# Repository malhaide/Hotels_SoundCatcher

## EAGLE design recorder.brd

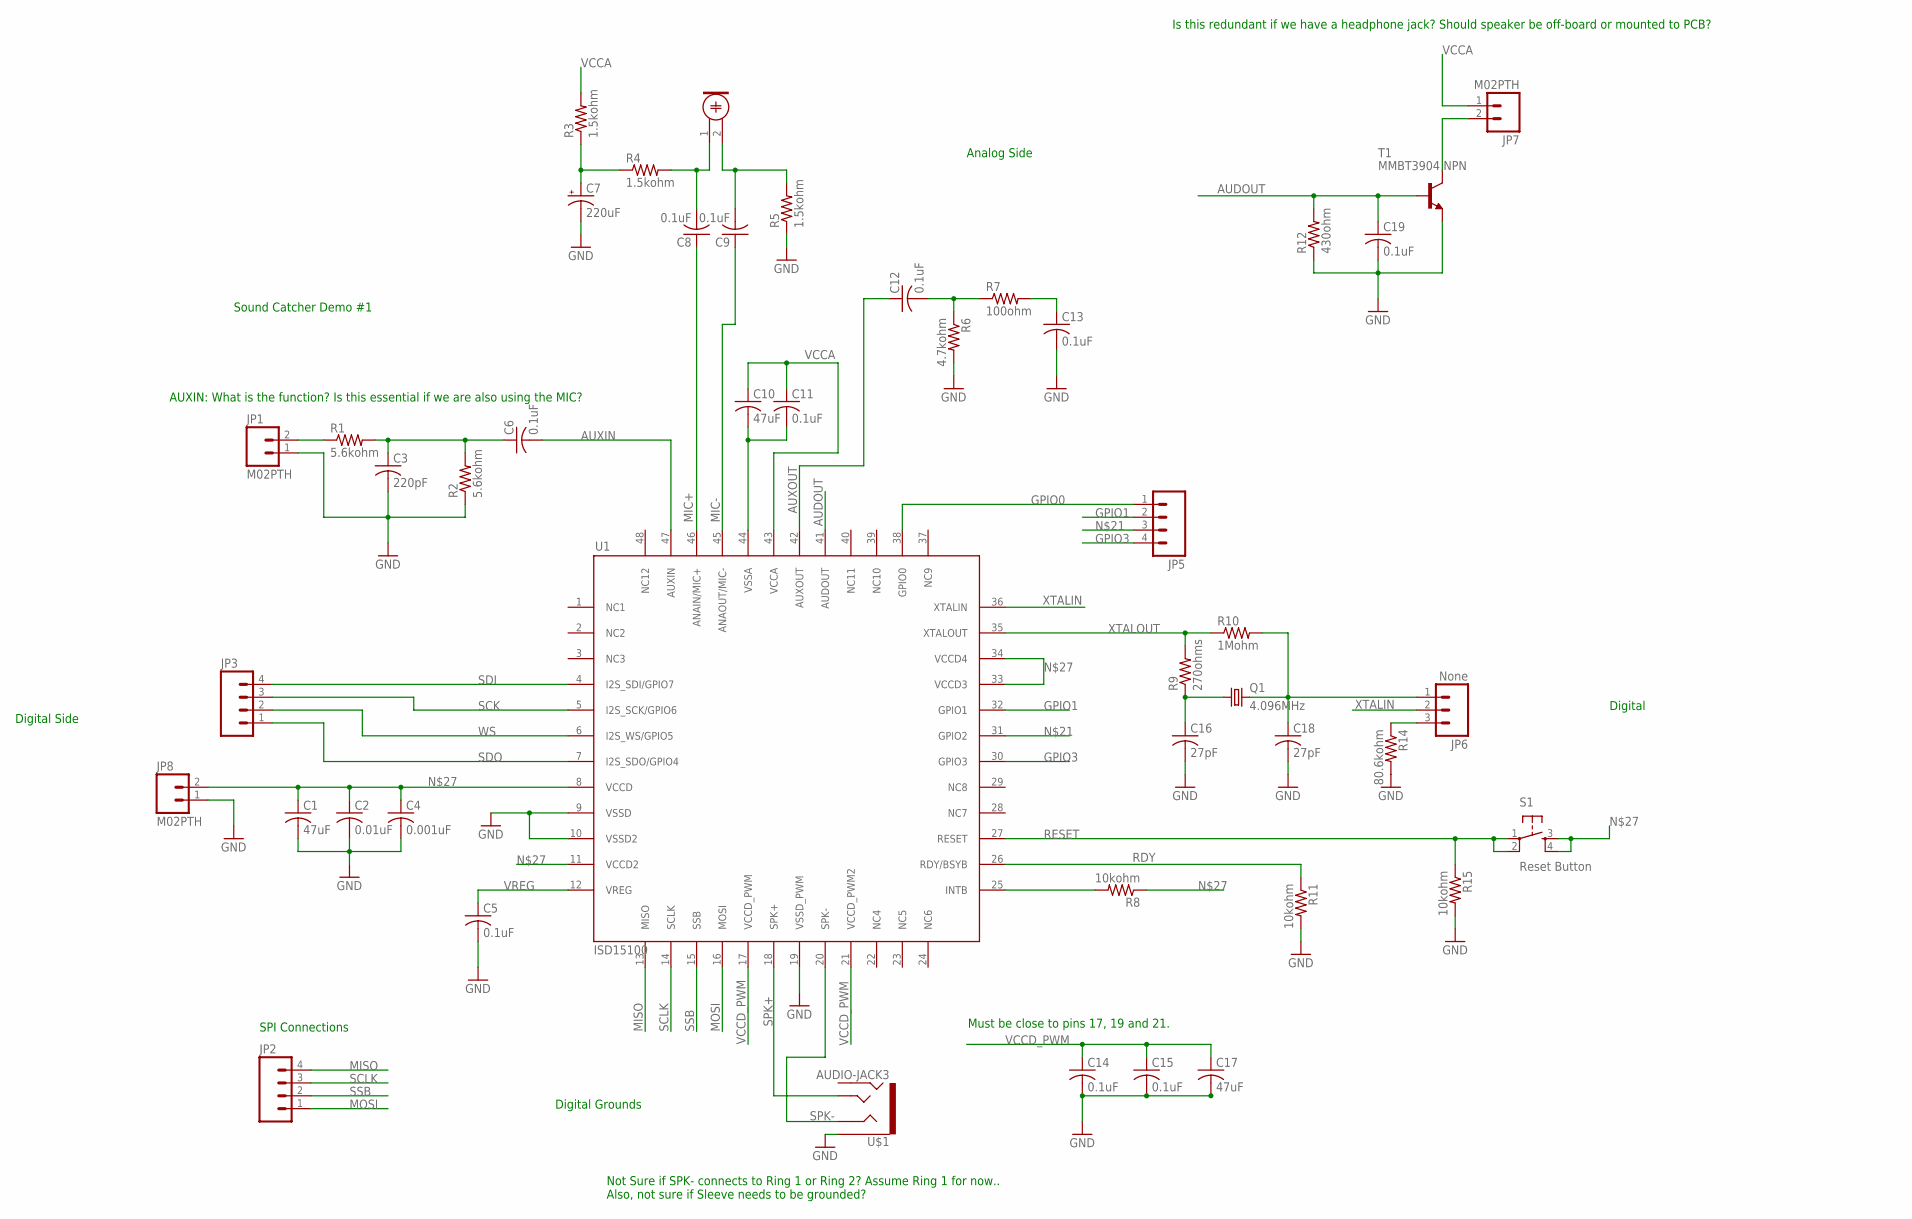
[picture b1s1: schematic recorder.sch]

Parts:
C1, C10, C17: 47uF; C1206
C2: 0.01uF; C0402
C3: 220pF; C0402
C4: 0.001uF; C0402
C5, C8, C9, C11, C12, C13, C14, C15, C19: 0.1uF; C0402
C6: 0.1uF; C0603
C7: 220uF; 175TMP-0808
C16, C18: 27pF; C0402
JP1, JP7, JP8: M02PTH; 1X02
JP2, JP3, JP5: M04PTH; 1X04
JP6: None; 1X03
M1: ELECTRET_MICROPHON-WM-61A; WM-61A
Q1: 4.096MHz; SM49
R1, R2: 5.6kohm; R0402
R3, R4, R5: 1.5kohm; R0201; MPN 0402ZD104KAT2A
R6: 4.7kohm; R0201; MPN 0402ZD104KAT2A
R7: 100ohm; R0201; MPN 0402ZD104KAT2A
R8, R11, R15: 10kohm; R0201; MPN 0402ZD104KAT2A
R9: 270ohms; R0201; MPN 0402ZD104KAT2A
R10: 1Mohm; R0201; MPN 0402ZD104KAT2A
R12: 430ohm; R0402
R14: 80.6kohm; R0402
S1: Reset Button; TACTILE-SWITCH-SMD
T1: MMBT3904 NPN; SOT23-BEC
U1: ISD15100; LQFP48
U$1: AUDIO-JACK3; AUDIO-JACK-TRRS-SMD

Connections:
AUDOUT: C19.1, R12.2, T1.B, U1.41 (AUDOUT)
AUXIN: C6.2, U1.47 (AUXIN)
AUXOUT: C12.1, U1.42 (AUXOUT)
GND: C1.2, C2.2, C3.2, C4.2, C5.2, C7.-, C13.2, C14.2, C15.2, C16.2, C17.2, C18.2, C19.2, JP1.1, JP8.1, R2.1, R5.1, R6.2, R11.2, R12.1, R14.2, R15.2, T1.E, U1.9 (VSSD), U1.10 (VSSD2), U1.19 (VSSD_PWM), U$1.EARTH
GPIO0: JP5.1, U1.38 (GPIO0)
GPIO1: JP5.2, U1.32 (GPIO1)
GPIO3: JP5.4, U1.30 (GPIO3)
MIC+: C8.1, U1.46 (ANAIN/MIC+)
MIC-: C9.1, U1.45 (ANAOUT/MIC-)
MISO: JP2.4, U1.13 (MISO)
MOSI: JP2.1, U1.16 (MOSI)
unnamed: C18.1, JP6.1, Q1.2, R10.2
unnamed: C16.1, Q1.1, R9.1
unnamed: C12.2, R6.1, R7.1
unnamed: R8.2, U1.25 (INTB)
unnamed: JP1.2, R1.1
unnamed: JP6.3, R14.1
unnamed: C3.1, C6.1, R1.2, R2.2
unnamed: JP7.2, T1.C
unnamed: C9.2, M1.2, R5.2
unnamed: C13.1, R7.2
unnamed: C10.2, C11.2, U1.44 (VSSA)
unnamed: JP5.3, U1.31 (GPIO2)
unnamed: C8.2, M1.1, R4.2
unnamed: C1.1, C2.1, C4.1, JP8.2, R8.1, S1.3, S1.4, U1.8 (VCCD), U1.11 (VCCD2), U1.33 (VCCD3), U1.34 (VCCD4)
unnamed: C7.+, R3.1, R4.1
RDY: R11.1, U1.26 (RDY/BSYB)
RESET: R15.1, S1.1, S1.2, U1.27 (RESET)
SCK: JP3.3, U1.5 (I2S_SCK/GPIO6)
SCLK: JP2.3, U1.14 (SCLK)
SDI: JP3.4, U1.4 (I2S_SDI/GPIO7)
SDO: JP3.1, U1.7 (I2S_SDO/GPIO4)
SPK+: U1.18 (SPK+), U$1.TIP
SPK-: U1.20 (SPK-), U$1.RING1
SSB: JP2.2, U1.15 (SSB)
VCCA: C10.1, C11.1, JP7.1, R3.2, U1.43 (VCCA)
VCCD_PWM: C14.1, C15.1, C17.1, U1.17 (VCCD_PWM), U1.21 (VCCD_PWM2)
VREG: C5.1, U1.12 (VREG)
WS: JP3.2, U1.6 (I2S_WS/GPIO5)
XTALIN: JP6.2, U1.36 (XTALIN)
XTALOUT: R9.2, R10.1, U1.35 (XTALOUT)

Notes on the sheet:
Sound Catcher Demo #1
Must be close to pins 17, 19 and 21.
AUXIN: What is the function? Is this essential if we are also using the MIC?
SPI Connections
Is this redundant if we have a headphone jack? Should speaker be off-board or mounted to PCB?
Digital Side
Digital Grounds
Digital
Analog Side
Not Sure if SPK- connects to Ring 1 or Ring 2? Assume Ring 1 for now.. Also, not sure if Sleeve needs to be grounded?

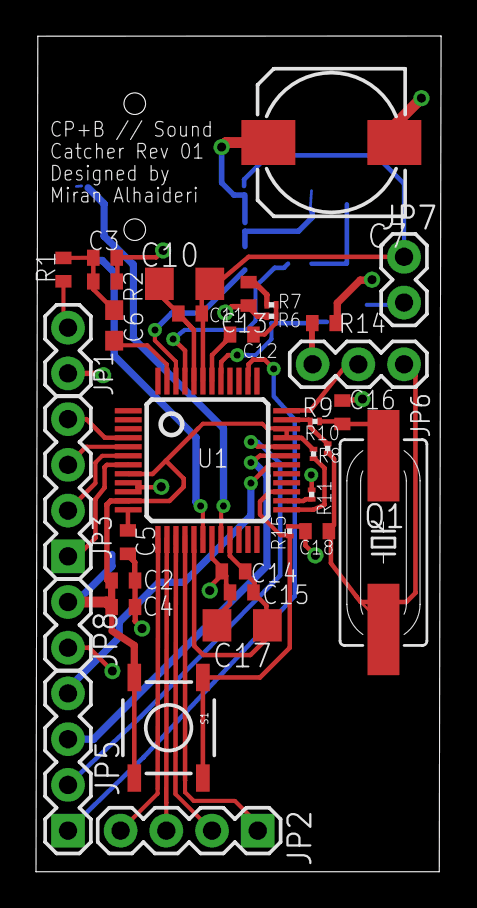
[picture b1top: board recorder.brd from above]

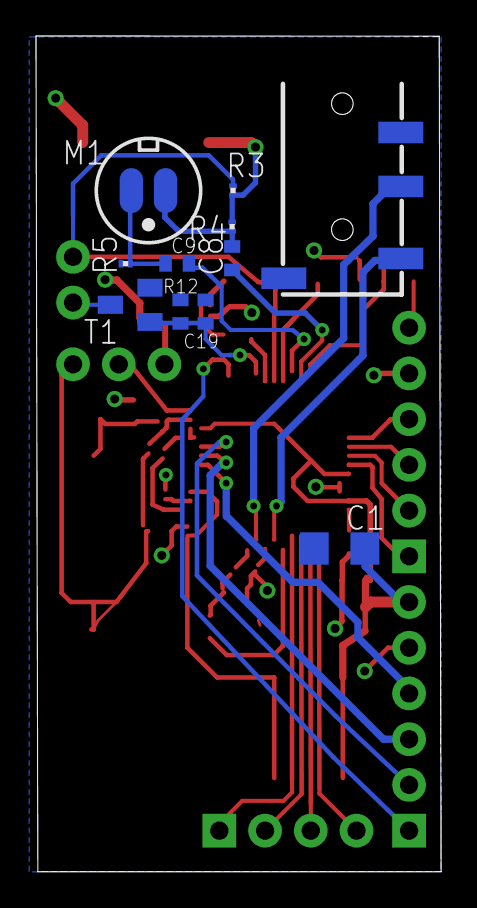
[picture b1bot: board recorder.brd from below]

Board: 2 copper layers, 22.5 x 46.4 mm, 46 parts (11 on the bottom side), 41 nets.

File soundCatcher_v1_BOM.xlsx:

Quantity | Designator | Description | Manufacturer | Manufacturer Part Number | Supplier 1 | Supplier Part Number 1 | Supplier Link | Notes
2 | C1, C10, C17 | CAP CER 47UF 6.3V 20% X5R 1206 | Murata | GRM31CR60J476ME19L | Digikey | 490-3907-1-ND | http://www.digikey.com/product-detail/en/GRM31CR60J476ME19L/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
1 | C2 | CAP CER 10000PF 10V 10% X7R 0402 | Samsung | CL05B103KP5NNNC | Digikey | 1276-1502-1-ND | http://www.digikey.com/product-detail/en/CL05B103KP5NNNC/127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
1 | C3 | CAP CER 220PF 16V 5% NP0 0402 | Samsung | CL05C221JO5NNNC | Digikey | 1276-1668-1-ND | http://www.digikey.com/product-detail/en/CL05C221JO5NNNC/127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
1 | C4 | CAP CER 1000PF 16V 10% X7R 0402 | Yageo | CC0402KRX7R7BB102 | Digikey | 311-1352-1-ND | http://www.digikey.com/product-detail/en/CC0402KRX7R7BB102/3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
10 | C5, C6, C8, C9, C11, C12, C13, C14, C15, C19 | 0.1uF C0402 Cer Cap | Taiyo Yuden | LMK105BJ104KV-F | Digikey | 587-1227-1-ND | http://www.digikey.com/product-detail/en/LMK105BJ104KV-F/587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
1 | C7 | CAP ALUM 220UF 10V 20% SMD | Nichicon | UWX1A221MCL1GB | Digikey | 493-2098-1-ND | http://www.digikey.com/product-detail/en/UWX1A221MCL1GB/493-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
 | C16, C18 | 27 pF C0402 Cer Cap | Murata | GRM1555C1E270JA01D | Digikey | 490-6176-1-ND | http://www.digikey.com/product-detail/en/GRM1555C1E270JA01D/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
1 | JP1, JP7, JP8 | 2-pin 0.1" male header (breakable) | Sparkfun | PRT-00116 | Sparkfun | PRT-00116 | https://www.sparkfun.com/products/116 | Break into either 2-pin, 3-pin, or 4-pin size
 | JP6 | 3-pin 0.1" male header (breakable)
 | JP2, JP3, JP5 | 4-in 0.1" male header (breakable)
1 | JP4 | 3.5 mm TRRS Audio Jack SMT |  |  | Sparkfun | PRT-12639 | https://www.sparkfun.com/products/12639
1 | M1 | Electret Microphone SMD; 20~20kHz | Panasonic | WM-61A | ebay | N/A | http://www.ebay.com/itm/like/350779217336?lpid=82
1 | Q1 | SM49 4.096 MHz XTAL | TXC Corporation | 9C-4.096MBBK-T | Digikey | 887-1828-1-ND | http://www.digikey.com/product-detail/en/9C-4.096MBBK-T/887-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
2 | R1, R2 | 5.6 kohm 0402 Res | Stackpole | RMCF0402JT5K60 | Digikey | RMCF0402JT5K60CT-ND | http://www.digikey.com/product-detail/en/RMCF0402JT5K60/RMCF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
3 | R3, R4, R5 | RES 1.5K OHM 1/20W 5% 0201 SMD | Yageo | RC0201JR-071K5L | Digikey | 311-1.5KNCT-ND | http://www.digikey.com/product-detail/en/RC0201JR-071K5L/311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
1 | R6 | 4.7 kohm 0201 Res | Panasonic | ERJ-1GNJ472C | Digikey | P4.7AECT-ND | http://www.digikey.com/product-detail/en/ERJ-1GNJ472C/P4.7AE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
1 | R7 | RES 100 OHM 1/20W 5% 0201 SMD | Rohm semiconductor | MCR006YRTJ101 | Digikey | RHM100CCCT-ND | http://www.digikey.com/product-detail/en/MCR006YRTJ101/RHM10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
3 | R8, R11, R15 | RES 10K OHM 1/20W 5% 0201 SMD | Yageo | RC0201JR-0710KL | Digikey | 311-10KNCT-ND | http://www.digikey.com/product-detail/en/RC0201JR-0710KL/311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
1 | R9 | 270 ohm 0201 Res | Panasonic | ERJ-1GEJ271C | Digikey | P270AGCT-ND | http://www.digikey.com/product-detail/en/ERJ-1GEJ271C/P270AG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
1 | R10 | RES 1M OHM 1/20W 5% 0201 SMD | Yageo | RC0201JR-071ML | Digikey | 311-1MNCT-ND | http://www.digikey.com/product-detail/en/RC0201JR-071ML/311-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
1 | R12 | 430 ohm 0402 Res | Yageo | RC0402FR-07430RL | Digikey | 311-430LRCT-ND | http://www.digikey.com/product-detail/en/RC0402FR-07430RL/31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
1 | R14 | 80.6 kohm R0402 Res | Stackpole | RMCF0402FT80K6 | Digi-Key | RMCF0402FT80K6CT-ND | http://www.digikey.com/product-detail/en/RMCF0402FT80K6/RMCF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
1 | S1 | Reset Button; SWITCH TACTILE SPST-NO 0.05A 12V | C&K Components | PTS525SM10SMTR LFS | Digi-Key | CKN9104CT-ND | http://www.digikey.com/product-detail/en/PTS525SM10SMTR%20LF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
1 | T1 | TRANSISTOR GP NPN AMP SOT-23 | Fairchild Semiconductor | MMBT3904LT1-NPN-SOT23-BEC | Digikey | MMBT3904FSCT-ND | http://www.digikey.com/product-detail/en/MMBT3904/MMBT3904FS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
1 | U1 | ISD15100 Audio IC; LQFP48 Pkg | Nuvoton | ISD15102FYI | Digi-Key | ISD15102FYI-ND | http://www.digikey.com/scripts/DkSearch/dksus.dll?Detail&ite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
Compulsory columns highlighted in yellow

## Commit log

2014-06-03 first commit. schematic and project file
2014-06-03 adding readme file
2014-06-05 Added board file and updated schematic/project files
2014-06-05 Oops.. forgot to re-add *.sch and *.epf files to last commit. Everything should be up to date now.
2014-06-05 rearranged dimensions of board
2014-06-06 Began routing PCB traces. Almost finished but vias are not connected
2014-06-07 Finished layout of PCB board. DRC mostly clean other than drill requirements, which can be adjusted
2014-06-09 spaced out component further for easier routing and to pass Sunstone DRC rules. Also, added VCC, GND 2-pin connector
2014-06-10 added design parameters readMe, BoM, changed C1 package to 1206
2014-06-10 repositioned silkscreen on top, bottom boards
2014-06-11 upodated BOM. changed mic, headphone jack, and other passive components
2014-06-12 moved gnd plane to bottom layer, added vias to gnd, and adjust components around to pass DRC
2014-06-12 added gerber files to design

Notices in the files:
parts and their libraries:
SparkFun-Connectors: Licensing: Creative Commons ShareAlike 4.0 International - https://creativecommons.org/licenses/by-sa/4.0
